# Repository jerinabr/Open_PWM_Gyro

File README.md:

# Open_PWM_Gyro
## Description
6-channel PWM gyro for fixed wing RC planes. Meant to be connected to an ELRS RX or other RX that outputs CRSF serial data.

### Layer Stackup
This is a 4-layer board with the following stackup:
1. Signal + Power
2. Ground
3. Ground
4. Signal + Power

Both ground layers are solid ground pours and aren't shown in the images section below

### Features
- USB-C for device firmware upgrade and configuration
- SWD header for device programming and debugging
- 2-color status LED (red, blue) controlled by the MCU
- Boot switch to allow the device to enter the bootloader on power-up
- 6-axis IMU (3-axis accelerometer, 3-axis gyroscope)
- Pin header for servo/ESC connections with one 3-pin group for serial data input from the RX

### Firmware
Firmware for this gyro can be found [in this repo](https://github.com/jerinabr/Open_PWM_Gyro_Firmware)

## BOM
| Reference             | Qty | Value                       | Footprint                                                             | DigiKey Part #                |
| --------------------- | --- | --------------------------- | --------------------------------------------------------------------- | ----------------------------- |
| C1,C5,C6,C7,C8,C9,C12 | 7   | 0.1u                        | Capacitor_SMD:C_0402_1005Metric_Pad0.74x0.62mm_HandSolder             | 1276-6720-1-ND                |
| C2,C4                 | 2   | 1u                          | Capacitor_SMD:C_0402_1005Metric_Pad0.74x0.62mm_HandSolder             | 1276-1445-1-ND                |
| C3                    | 1   | 22u                         | Capacitor_SMD:CP_Elec_4x5.4                                           | 732-8413-1-ND                 |
| C10,C11               | 2   | 10p                         | Capacitor_SMD:C_0402_1005Metric_Pad0.74x0.62mm_HandSolder             | 311-1014-1-ND                 |
| D1                    | 1   | PMEG2005CT,215              | Package_TO_SOT_SMD:SOT-23                                             | 1727-5188-2-ND                |
| J1                    | 1   | USB_C_Receptacle_USB2.0_16P | Connector_USB:USB_C_Receptacle_GCT_USB4105-xx-A_16P_TopMnt_Horizontal | 2073-USB4105-GF-ATR-ND        |
| J2                    | 1   | Conn_01x21                  | Connector_PinHeader_2.54mm_Custom:PinHeader_3x07_P2.54mm_Vertical     | TSW-107-26-F-T-ND             |
| LED1                  | 1   | LED_Dual_AKKA               | LED_SMD_Custom:LED_APHBM2012QBDSURKC                                  | 754-1506-1-ND                 |
| MT1                   | 1   | ICM-42605                   | Package_LGA_Custom:XDCR_ICM-42605                                     | 1428-1152-1-ND                |
| R1,R2                 | 2   | 5k1                         | Resistor_SMD:R_0402_1005Metric_Pad0.72x0.64mm_HandSolder              | 13-RC0402FR-135K1LCT-ND       |
| R3,R5                 | 2   | 10k                         | Resistor_SMD:R_0402_1005Metric_Pad0.72x0.64mm_HandSolder              | 311-10KJRCT-ND                |
| R4                    | 1   | 68                          | Resistor_SMD:R_0402_1005Metric_Pad0.72x0.64mm_HandSolder              | 311-68.0LRCT-ND               |
| SW1                   | 1   | SW_SPST                     | Button_Switch_SMD_Custom:R-667995_MIT                                 | 2508-R-667995TR-ND            |
| SWD1                  | 1   | Conn_02x05_Odd_Even         | Connector_PinHeader_1.27mm:PinHeader_2x05_P1.27mm_Vertical            | S9015E-05-ND                  |
| U1                    | 1   | TCR2EF33_LMCT               | Package_TO_SOT_SMD_Custom:SOT-25 SMV_TOS                              | TCR2EF33LM(CTTR-ND            |
| U2                    | 1   | STM32G431KBTx               | Package_QFP:LQFP-32_7x7mm_P0.8mm                                      | 497-19470-ND                  |
| Y1                    | 1   | Crystal_GND24               | Crystal_Custom:Crystal_SMD_ECS_ECX_2236-4Pin_2.5x2.0mm                | 50-ECS-160-10-36-CKM-TR3TR-ND |

> [!NOTE]
> J2 is a 3x7 2.54mm pitch pin header. This part can be replaced with three 7-pin headers or seven 3-pin headers or some other combination to save cost

## Images
### Schematic
#### Page 1: Power + Connectors

#### Page 2: MCU + IMU

### PCB
#### Top Layer

#### Bottom Layer

#### Top + Bottom Layer

### 3D View
#### Top

#### Bottom

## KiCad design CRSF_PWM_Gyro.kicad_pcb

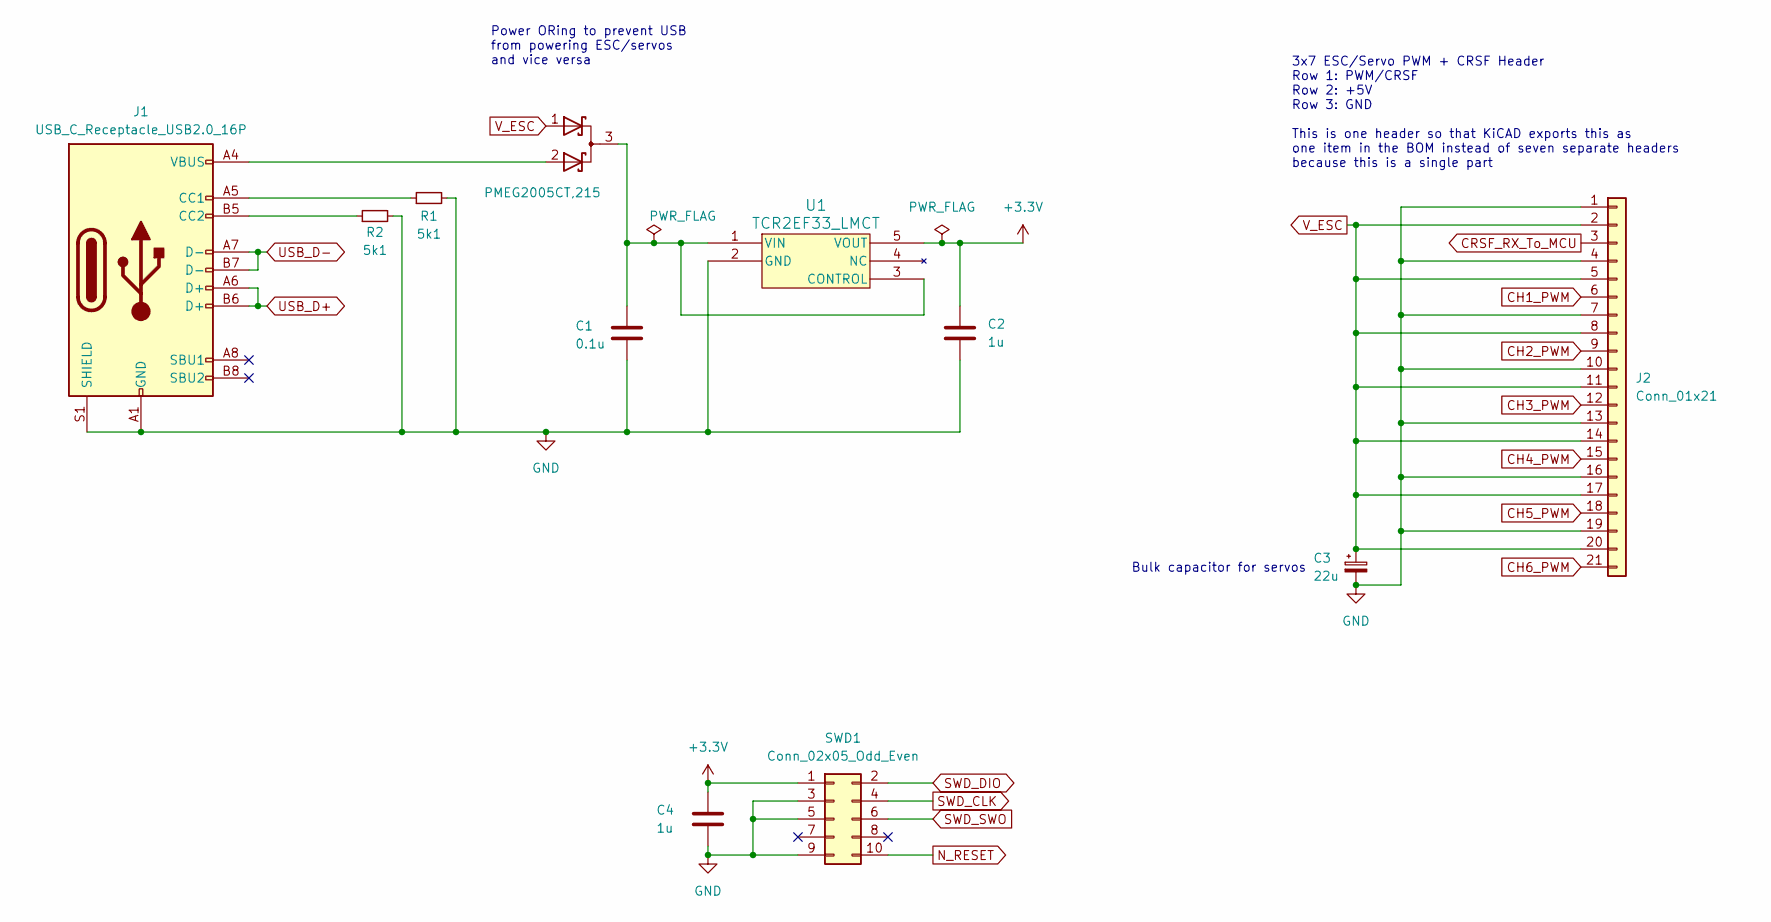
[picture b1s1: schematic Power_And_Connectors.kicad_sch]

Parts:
C1: 0.1u; C_0402_1005Metric_Pad0.74x0.62mm_HandSolder; Mfg Part # CL05B104KA5NNNC; DigiKey Part # 1276-6720-1-ND
C2, C4: 1u; C_0402_1005Metric_Pad0.74x0.62mm_HandSolder; Mfg Part # CL05A105KA5NQNC; DigiKey Part # 1276-1445-1-ND
C3: 22u; CP_Elec_4x5.4; Mfg Part # 865080340003; DigiKey Part # 732-8413-1-ND
D1: PMEG2005CT,215; SOT-23; Mfg Part # PMEG2005CT,215; DigiKey Part # 1727-5188-2-ND
J1: USB_C_Receptacle_USB2.0_16P; USB_C_Receptacle_GCT_USB4105-xx-A_16P_TopMnt_Horizontal; Mfg Part # USB4105-GF-A; DigiKey Part # 2073-USB4105-GF-ATR-ND
J2: Conn_01x21; PinHeader_3x07_P2.54mm_Vertical; Mfg Part # TSW-107-26-F-T; DigiKey Part # TSW-107-26-F-T-ND
R1, R2: 5k1; R_0402_1005Metric_Pad0.72x0.64mm_HandSolder; Mfg Part # RC0402FR-135K1L; DigiKey Part # 13-RC0402FR-135K1LCT-ND
SWD1: Conn_02x05_Odd_Even; PinHeader_2x05_P1.27mm_Vertical; Mfg Part # GRPB052VWVN-RC; DigiKey Part # S9015E-05-ND
U1: TCR2EF33_LMCT; SOT-25 SMV_TOS; Mfg Part # TCR2EF33,LM(CT; DigiKey Part # TCR2EF33LM(CTTR-ND

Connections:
+3.3V: C2.1, C4.1, SWD1.1, U1.5 (VOUT); also elsewhere on the board
CH1_PWM: J2.6; also elsewhere on the board
CH2_PWM: J2.9; also elsewhere on the board
CH3_PWM: J2.12; also elsewhere on the board
CH4_PWM: J2.15; also elsewhere on the board
CH5_PWM: J2.18; also elsewhere on the board
CH6_PWM: J2.21; also elsewhere on the board
CRSF_RX_To_MCU: J2.3; also elsewhere on the board
GND: C1.2, C2.2, C3.2, C4.2, J1.A1 (GND), J1.A12 (GND), J1.B1 (GND), J1.B12 (GND), J1.S1 (SHIELD), J2.1, J2.4, J2.7, J2.10, J2.13, J2.16, J2.19, R1.2, R2.2, SWD1.3, SWD1.5, SWD1.9, U1.2 (GND); also elsewhere on the board
N_RESET: SWD1.10; also elsewhere on the board
unnamed: D1.2 (A), J1.A4 (VBUS), J1.A9 (VBUS), J1.B4 (VBUS), J1.B9 (VBUS)
unnamed: C1.1, D1.3 (K), U1.1 (VIN), U1.3 (CONTROL)
unnamed: J1.A5 (CC1), R1.1
unnamed: J1.B5 (CC2), R2.1
SWD_CLK: SWD1.4; also elsewhere on the board
SWD_DIO: SWD1.2; also elsewhere on the board
SWD_SWO: SWD1.6; also elsewhere on the board
USB_D+: J1.A6 (D+), J1.B6 (D+); also elsewhere on the board
USB_D-: J1.A7 (D-), J1.B7 (D-); also elsewhere on the board
V_ESC: C3.1, D1.1 (A), J2.2, J2.5, J2.8, J2.11, J2.14, J2.17, J2.20

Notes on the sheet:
Bulk capacitor for servos
Power ORing to prevent USB from powering ESC/servos and vice versa
3x7 ESC/Servo PWM + CRSF Header Row 1: PWM/CRSF Row 2: +5V Row 3: GND This is one header so that KiCAD exports this as one item in the BOM instead of seven separate headers because this is a single part

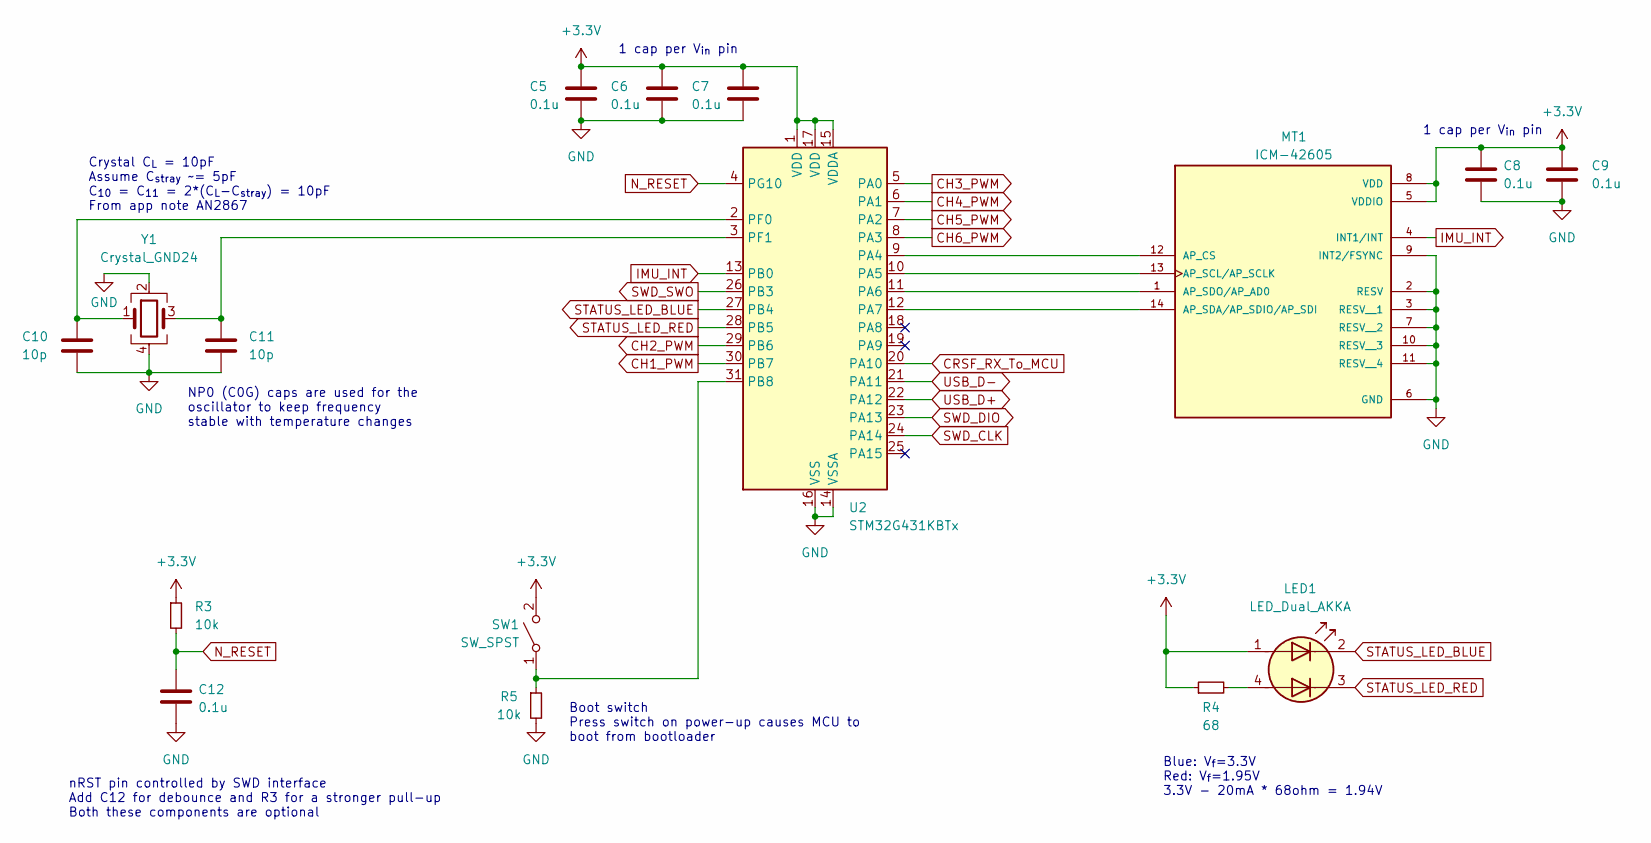
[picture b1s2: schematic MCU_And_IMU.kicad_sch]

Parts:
C5, C6, C7, C8, C9, C12: 0.1u; C_0402_1005Metric_Pad0.74x0.62mm_HandSolder; Mfg Part # CL05B104KA5NNNC; DigiKey Part # 1276-6720-1-ND
C10, C11: 10p; C_0402_1005Metric_Pad0.74x0.62mm_HandSolder; Mfg Part # CC0402JRNPO9BN100; DigiKey Part # 311-1014-1-ND
LED1: LED_Dual_AKKA; LED_APHBM2012QBDSURKC; Mfg Part # APHBM2012QBDSURKC; DigiKey Part # 754-1506-1-ND
MT1: ICM-42605; XDCR_ICM-42605; PARTREV 1.7; DigiKey Part # 1428-1152-1-ND
R3, R5: 10k; R_0402_1005Metric_Pad0.72x0.64mm_HandSolder; Mfg Part # RC0402JR-0710KL; DigiKey Part # 311-10KJRCT-ND
R4: 68; R_0402_1005Metric_Pad0.72x0.64mm_HandSolder; Mfg Part # RC0402FR-0768RL; DigiKey Part # 311-68.0LRCT-ND
SW1: SW_SPST; R-667995_MIT; Mfg Part # R-667995; DigiKey Part # 2508-R-667995TR-ND
U2: STM32G431KBTx; LQFP-32_7x7mm_P0.8mm; Mfg Part # STM32G431KBT6; DigiKey Part # 497-19470-ND
Y1: Crystal_GND24; Crystal_SMD_ECS_ECX_2236-4Pin_2.5x2.0mm; Mfg Part # ECS-160-10-36-CKM-TR3; DigiKey Part # 50-ECS-160-10-36-CKM-TR3TR-ND

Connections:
+3.3V: C5.1, C6.1, C7.1, C8.1, C9.1, LED1.1 (A1), MT1.5 (VDDIO), MT1.8 (VDD), R3.1, R4.1, SW1.2 (B), U2.1 (VDD), U2.15 (VDDA), U2.17 (VDD); also elsewhere on the board
CH1_PWM: U2.30 (PB7); also elsewhere on the board
CH2_PWM: U2.29 (PB6); also elsewhere on the board
CH3_PWM: U2.5 (PA0); also elsewhere on the board
CH4_PWM: U2.6 (PA1); also elsewhere on the board
CH5_PWM: U2.7 (PA2); also elsewhere on the board
CH6_PWM: U2.8 (PA3); also elsewhere on the board
CRSF_RX_To_MCU: U2.20 (PA10); also elsewhere on the board
GND: C5.2, C6.2, C7.2, C8.2, C9.2, C10.2, C11.2, C12.2, MT1.2 (RESV), MT1.3 (RESV__1), MT1.6 (GND), MT1.7 (RESV__2), MT1.9 (INT2/FSYNC), MT1.10 (RESV__3), MT1.11 (RESV__4), R5.2, U2.14 (VSSA), U2.16 (VSS), U2.32 (VSS), Y1.2, Y1.4; also elsewhere on the board
IMU_INT: MT1.4 (INT1/INT), U2.13 (PB0)
N_RESET: C12.1, R3.2, U2.4 (PG10); also elsewhere on the board
unnamed: LED1.4 (A2), R4.2
unnamed: MT1.12 (AP_CS), U2.9 (PA4)
unnamed: MT1.13 (AP_SCL/AP_SCLK), U2.10 (PA5)
unnamed: MT1.14 (AP_SDA/AP_SDIO/AP_SDI), U2.12 (PA7)
unnamed: MT1.1 (AP_SDO/AP_AD0), U2.11 (PA6)
unnamed: R5.1, SW1.1 (A), U2.31 (PB8)
unnamed: C10.1, U2.2 (PF0), Y1.1
unnamed: C11.1, U2.3 (PF1), Y1.3
STATUS_LED_BLUE: LED1.2 (K1), U2.27 (PB4)
STATUS_LED_RED: LED1.3 (K2), U2.28 (PB5)
SWD_CLK: U2.24 (PA14); also elsewhere on the board
SWD_DIO: U2.23 (PA13); also elsewhere on the board
SWD_SWO: U2.26 (PB3); also elsewhere on the board
USB_D+: U2.22 (PA12); also elsewhere on the board
USB_D-: U2.21 (PA11); also elsewhere on the board

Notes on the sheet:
NP0 (C0G) caps are used for the oscillator to keep frequency stable with temperature changes
Blue: V_{f}=3.3V Red: V_{f}=1.95V 3.3V - 20mA * 68ohm = 1.94V
1 cap per V_{in} pin
Boot switch Press switch on power-up causes MCU to boot from bootloader
nRST pin controlled by SWD interface Add C12 for debounce and R3 for a stronger pull-up Both these components are optional
Crystal C_{L} = 10pF Assume C_{stray} ~= 5pF C_{10} = C_{11} = 2*(C_{L}-C_{stray}) = 10pF From app note AN2867

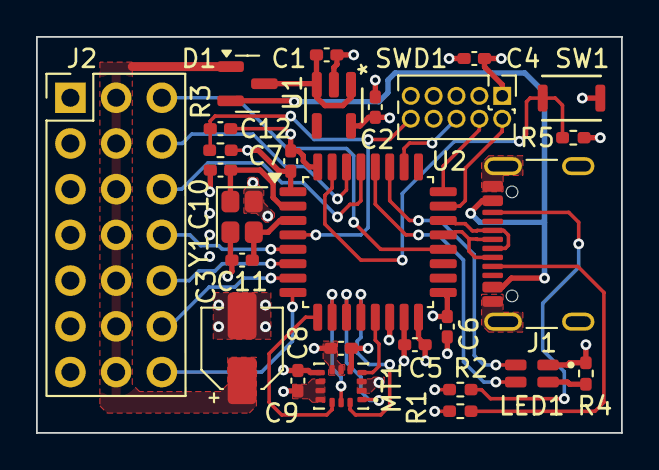
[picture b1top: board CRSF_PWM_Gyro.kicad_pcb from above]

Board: 4 copper layers, 32.5 x 22.0 mm, 27 parts (0 on the bottom side), 31 nets.

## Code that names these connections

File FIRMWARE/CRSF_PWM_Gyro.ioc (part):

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Mcu.Name=STM32G431K(6-8-B)Tx
Mcu.Package=LQFP32
Mcu.UserName=STM32G431KBTx
PA0.Signal=S_TIM2_CH1
PA1.Signal=S_TIM2_CH2
PA10.Mode=Asynchronous
PA10.Signal=USART1_RX
PA11.Mode=Device
PA11.Signal=USB_DM
PA12.Mode=Device
PA12.Signal=USB_DP
PA13.Mode=Trace_Asynchronous_SW
PA13.Signal=SYS_JTMS-SWDIO
PA14.Mode=Trace_Asynchronous_SW
PA14.Signal=SYS_JTCK-SWCLK
PA2.Signal=S_TIM2_CH3
PA3.Signal=S_TIM2_CH4
PA4.Mode=NSS_Signal_Hard_Output
PA4.Signal=SPI1_NSS
PA5.Mode=Full_Duplex_Master
PA5.Signal=SPI1_SCK
PA6.Mode=Full_Duplex_Master
PA6.Signal=SPI1_MISO
PA7.Mode=Full_Duplex_Master
PA7.Signal=SPI1_MOSI
PA9.Mode=Asynchronous
PA9.Signal=USART1_TX
PB0.GPIOParameters=GPIO_Label
PB0.GPIO_Label=IMU_INT
PB0.Signal=GPXTI0
PB3.Mode=Trace_Asynchronous_SW
PB3.Signal=SYS_JTDO-SWO
PB4.GPIOParameters=GPIO_Label
PB4.GPIO_Label=RED_LED
PB4.Signal=GPIO_Output
PB5.GPIOParameters=GPIO_Label
PB5.GPIO_Label=BLUE_LED
PB5.Signal=GPIO_Output
PB6.Signal=S_TIM4_CH1
PB7.Signal=S_TIM3_CH4
PF0-OSC_IN.Mode=HSE-External-Oscillator
PF0-OSC_IN.Signal=RCC_OSC_IN
PF1-OSC_OUT.Mode=HSE-External-Oscillator
PF1-OSC_OUT.Signal=RCC_OSC_OUT
RCC.HSE_VALUE=16000000
RCC.SYSCLKFreq_VALUE=160000000
RCC.SYSCLKSource=RCC_SYSCLKSOURCE_PLLCLK
board=custom

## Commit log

2025-05-26 Add main components to schematic
2025-05-29 Move hardware files into hardware folder
2025-05-29 Add firmware with placeholder file
2025-05-31 Pick different MCU and add USB C connector
2025-06-04 Add CRSF header and replace MCU with KB variant
2025-06-06 Separate schematic into pages
2025-06-07 Update footprints and add all PNs
2025-06-08 Create initial project with final pinout
2025-06-08 Swap PWM channels and initial PCB layout
2025-06-12 Update components and layout
2025-06-14 Made footprint updates
2025-06-15 Complete initial routing
2025-06-15 Add images and BOM CSV
2025-06-15 Make minor routing changes
2025-06-16 Add other fields to BOM
2025-06-19 Add .DS_Store to gitignore
2025-06-22 Clean up routing and layout
2025-06-22 Move some silkscreen text
2025-06-22 Update images
2025-06-23 Add gerbers and change file structure
2025-06-26 Rename project and update gerbers
2025-06-26 Rename bom file and add to bom folder
